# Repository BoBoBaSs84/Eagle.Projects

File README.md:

# Eagle.Projects

All of my Autodesk EAGLE projects are stored here.

## List of projects

- [Medium Wave Radio Transmitter](https://github.com/BoBoBaSs84/Eagle.Projects/tree/main/projects/MediumWaveRadioTransmitter)
- [Morley Power Wah Boost](https://github.com/BoBoBaSs84/Eagle.Projects/tree/main/projects/MorleyPowerWahBoost)
- [RGB Test Pattern Generator](https://github.com/BoBoBaSs84/Eagle.Projects/tree/main/projects/RGB-TestPatternGenerator)

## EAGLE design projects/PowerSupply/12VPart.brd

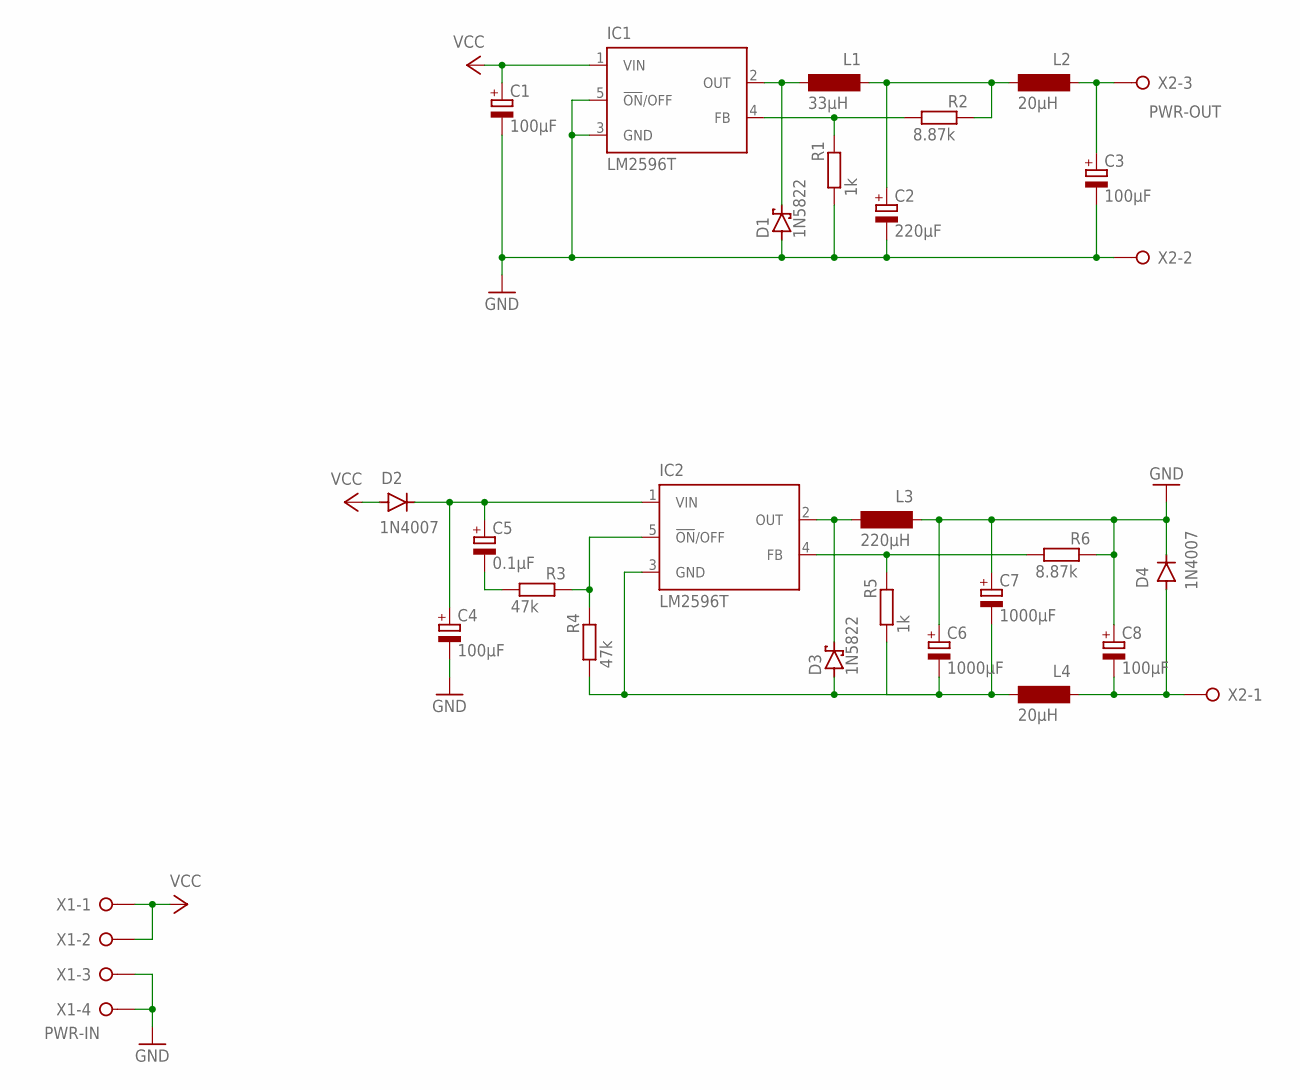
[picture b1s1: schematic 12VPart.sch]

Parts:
C1, C3, C4, C8: 100µF; E2,5-6
C2: 220µF; E2,5-6
C5: 0.1µF; E2-4
C6, C7: 1000µF; E5-10,5
D1, D3: 1N5822; C4111-15
D2, D4: 1N4007; DO-41
IC1, IC2: LM2596T; T05D
L1: 33µH; IND-120
L2, L4: 20µH; B82111B
L3: 220µH; 11PHC
R1, R5: 1k; 0207/10
R2, R6: 8.87k; 0207/10
R3, R4: 47k; 0207/10
X1: PWR-IN; W237-4P
X2: PWR-OUT; W237-133

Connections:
GND: C1.-, C2.-, C3.-, C4.-, C6.+, C7.+, C8.+, D1.A, D4.C, IC1.3 (GND), IC1.5 (!ON!/OFF), L3.P$2 (2), R1.1, R6.2, X1.3, X1.4, X2.2
unnamed: C4.+, C5.+, D2.C, IC2.1 (VIN)
unnamed: C8.-, D4.A, L4.P$2 (2), X2.1
unnamed: D1.C, IC1.2 (OUT), L1.P$1 (1)
unnamed: IC1.4 (FB), R1.2, R2.1
unnamed: C2.+, L1.P$2 (2), L2.P$1 (1), R2.2
unnamed: C3.+, L2.P$2 (2), X2.3
unnamed: C5.-, R3.1
unnamed: IC2.5 (!ON!/OFF), R3.2, R4.2
unnamed: C6.-, C7.-, D3.A, IC2.3 (GND), L4.P$1 (1), R4.1, R5.1
unnamed: D3.C, IC2.2 (OUT), L3.P$1 (1)
unnamed: IC2.4 (FB), R5.2, R6.1
VCC: C1.+, D2.A, IC1.1 (VIN), X1.1, X1.2

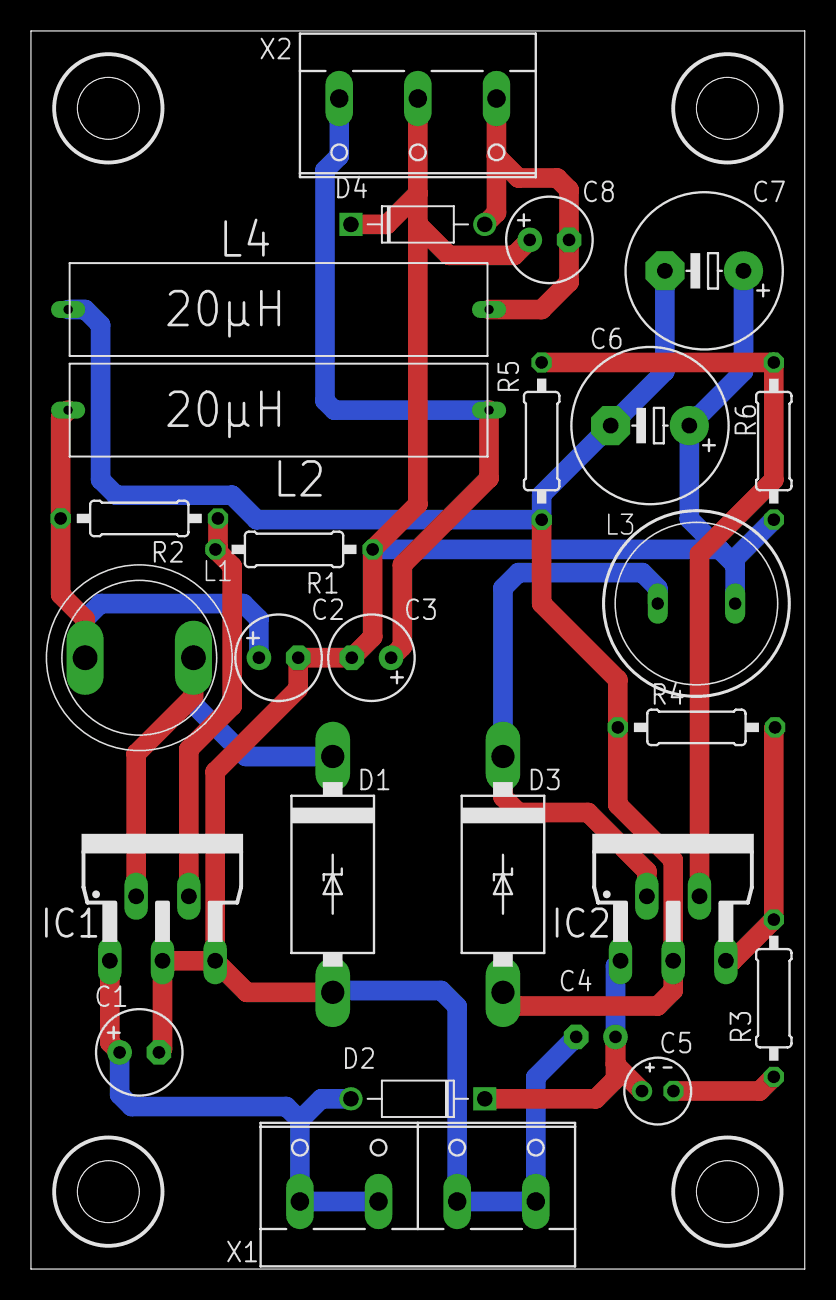
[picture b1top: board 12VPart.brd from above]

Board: 2 copper layers, 50.0 x 80.0 mm, 26 parts (1 on the bottom side), 13 nets.

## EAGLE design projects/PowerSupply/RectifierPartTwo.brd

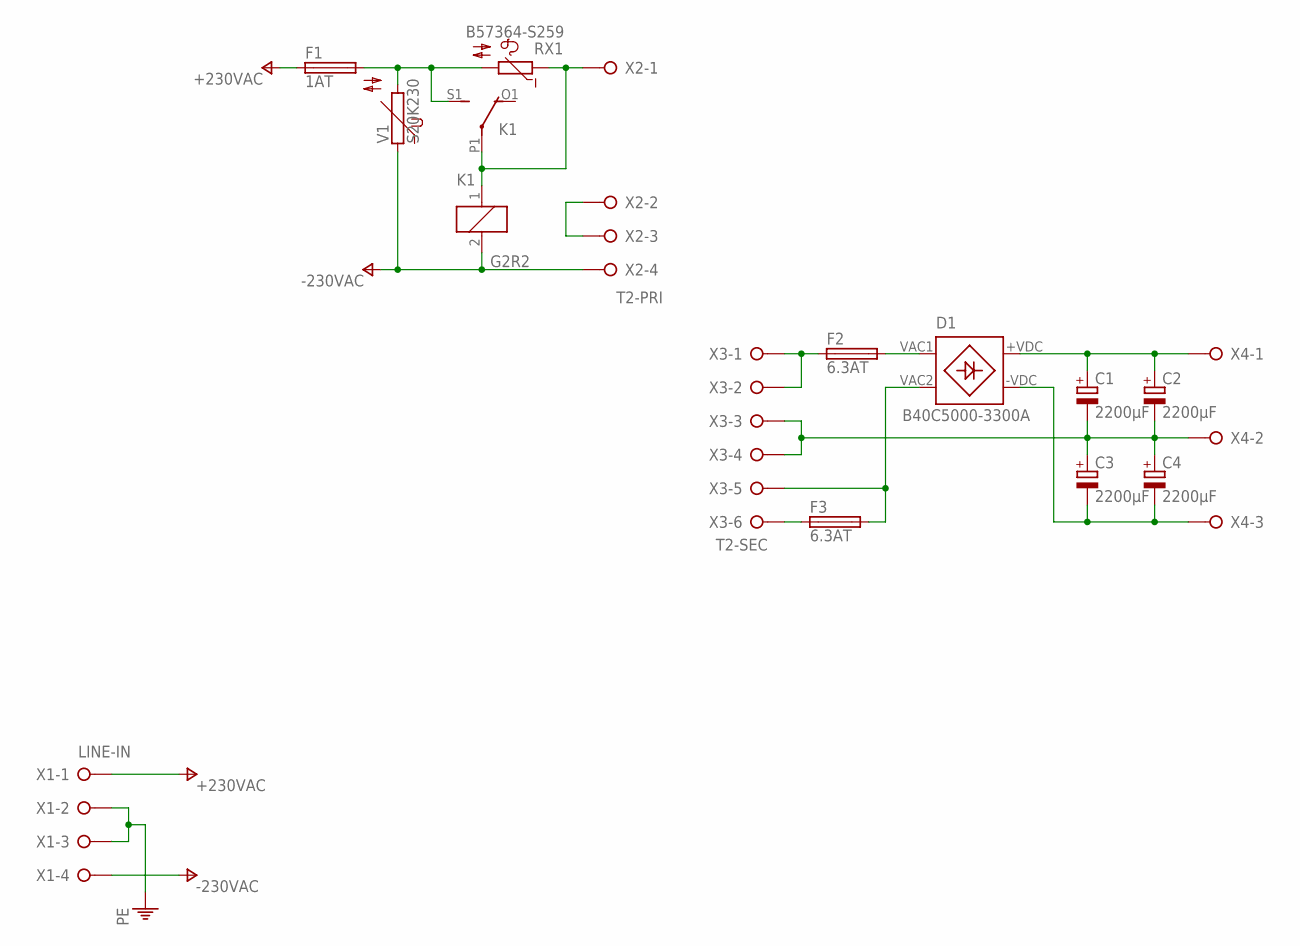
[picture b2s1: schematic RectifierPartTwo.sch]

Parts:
C1, C2, C3, C4: 2200µF; E7,5-16
D1: B40C5000-3300A; B..C
F1: 1AT; SH22,5A
F2, F3: 6.3AT; SH22,5A
K1: G2R2
RX1: B57364-S259; B57364S0
V1: S20K230
X1: LINE-IN; W237-4P
X2: T2-PRI; W237-4P
X3: T2-SEC; W237-6P
X4: W237-03P; W237-133

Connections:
+230VAC: F1.1, X1.1
-230VAC: K1.2, V1.1, X1.4, X2.4
unnamed: D1.VAC2, F3.2, X3.5
unnamed: F2.1, X3.1, X3.2
unnamed: C3.-, C4.-, D1.-VDC, X4.3
unnamed: F3.1, X3.6
unnamed: C1.+, C2.+, D1.+VDC, X4.1
unnamed: C1.-, C2.-, C3.+, C4.+, X3.3, X3.4, X4.2
unnamed: D1.VAC1, F2.2
unnamed: F1.2, K1.S1 (S), RX1.P$2 (2), V1.2
unnamed: X2.2, X2.3
unnamed: K1.1, K1.P1, RX1.P$1 (1), X2.1
PE: X1.2, X1.3

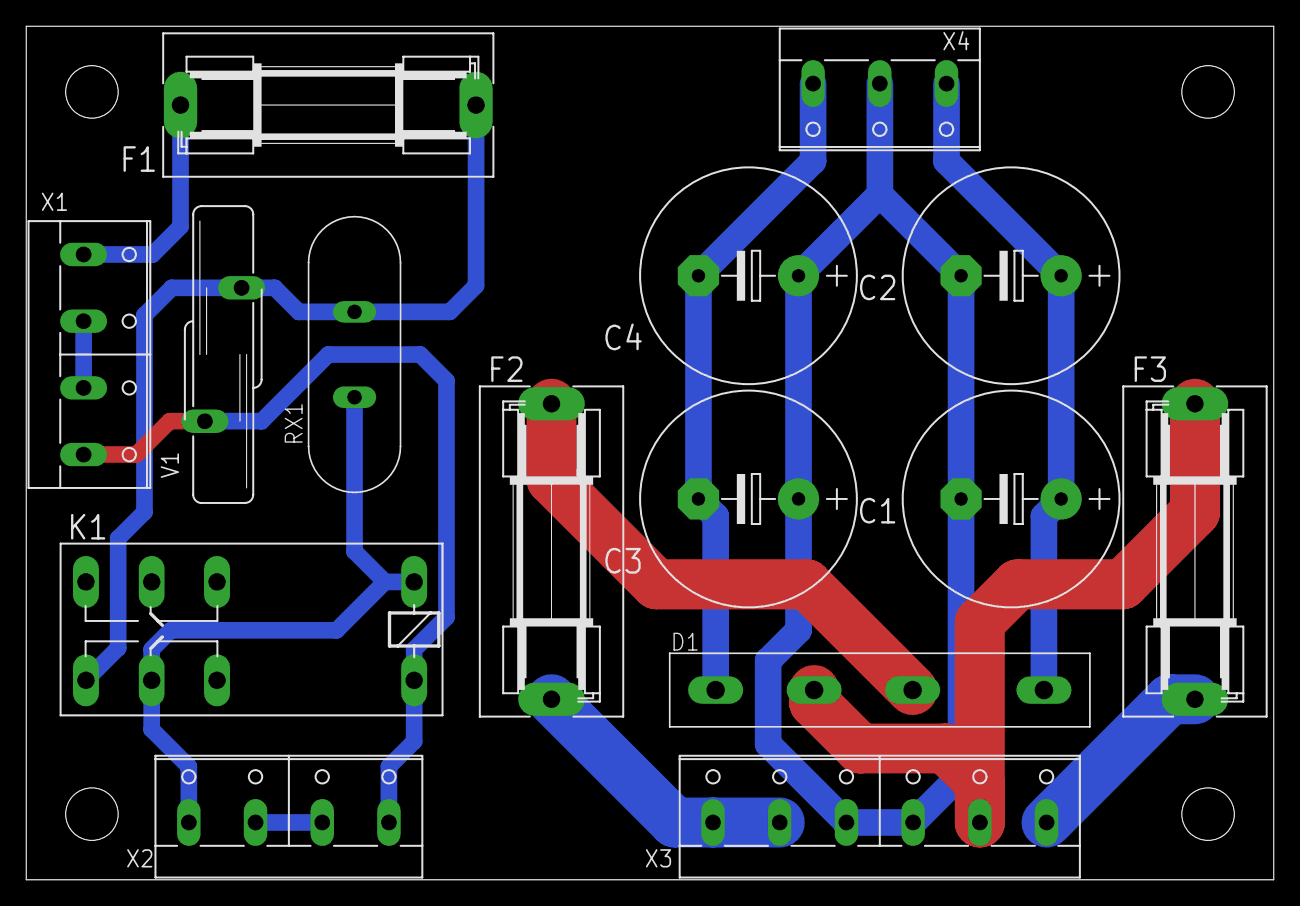
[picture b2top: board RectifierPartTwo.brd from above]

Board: 2 copper layers, 95.0 x 65.0 mm, 15 parts (0 on the bottom side), 13 nets.

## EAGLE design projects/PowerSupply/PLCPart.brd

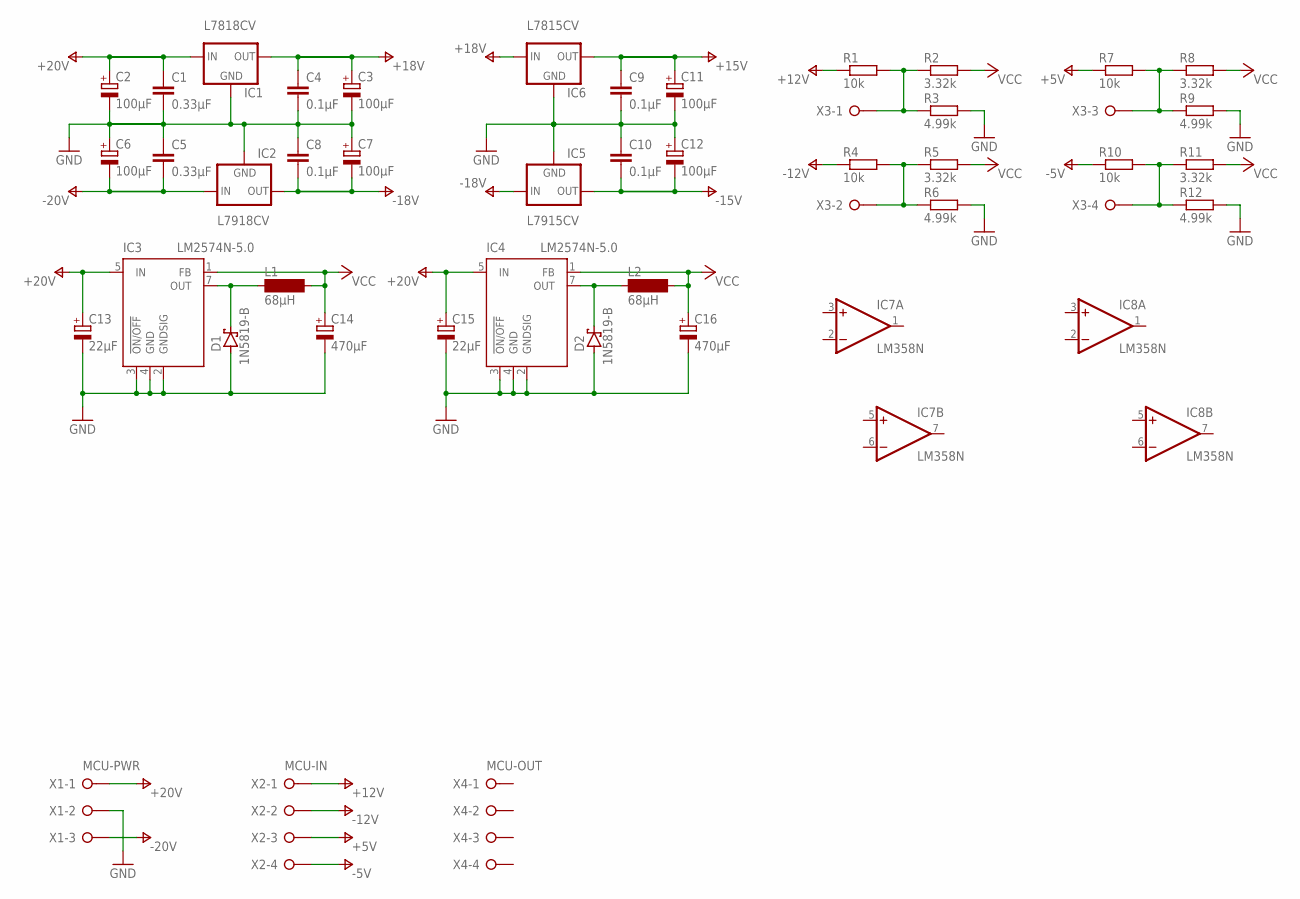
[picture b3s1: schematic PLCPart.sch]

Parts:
C1, C5: 0.33µF; C050-024X044
C2, C3, C6, C7, C11, C12: 100µF; E2,5-6
C4, C8, C9, C10: 0.1µF; C050-024X044
C13, C15: 22µF; E2-5
C14, C16: 470µF; E2-5
D1, D2: 1N5819-B; DO41-7.6
IC1: L7818CV; 78XXS
IC2: L7918CV; 79XXS
IC3, IC4: LM2574N-5.0; DIL08
IC5: L7915CV; 79XXS
IC6: L7815CV; 78XXS
IC7, IC8: LM358N; DIL08
L1, L2: 68µH; SD12K100
R1, R4, R7, R10: 10k; 0207/10
R2, R5, R8, R11: 3.32k; 0207/10
R3, R6, R9, R12: 4.99k; 0207/10
X1: MCU-PWR; W237-133
X2: MCU-IN; W237-4P
X3: W237-04P; W237-4P
X4: MCU-OUT; W237-4P

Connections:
+5V: R7.1, X2.3
+12V: R1.1, X2.1
+15V: C9.1, C11.+, IC6.OUT
+18V: C3.+, C4.1, IC1.OUT, IC6.IN
+20V: C1.1, C2.+, C13.+, C15.+, IC1.IN, IC3.5 (IN), IC4.5 (IN), X1.1
-5V: R10.1, X2.4
-12V: R4.1, X2.2
-15V: C10.2, C12.-, IC5.OUT
-18V: C7.-, C8.2, IC2.OUT, IC5.IN
-20V: C5.2, C6.-, IC2.IN, X1.3
GND: C1.2, C2.-, C3.-, C4.2, C5.1, C6.+, C7.+, C8.1, C9.2, C10.1, C11.-, C12.+, C13.-, C14.-, C15.-, C16.-, D1.A, D2.A, IC1.GND, IC2.GND, IC3.2 (GNDSIG), IC3.3 (!ON/OFF), IC3.4 (GND), IC4.2 (GNDSIG), IC4.3 (!ON/OFF), IC4.4 (GND), IC5.GND, IC6.GND, R3.2, R6.2, R9.2, R12.2, X1.2
unnamed: R1.2, R2.1, R3.1, X3.1
unnamed: R4.2, R5.1, R6.1, X3.2
unnamed: R7.2, R8.1, R9.1, X3.3
unnamed: R10.2, R11.1, R12.1, X3.4
unnamed: D1.C, IC3.7 (OUT), L1.1
unnamed: D2.C, IC4.7 (OUT), L2.1
V+: IC7.8 (V+), IC8.8 (V+)
V-: IC7.4 (V-), IC8.4 (V-)
VCC: C14.+, C16.+, IC3.1 (FB), IC4.1 (FB), L1.2, L2.2, R2.2, R5.2, R8.2, R11.2

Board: 2 copper layers, 44 parts (0 on the bottom side), 20 nets, no tracks yet.

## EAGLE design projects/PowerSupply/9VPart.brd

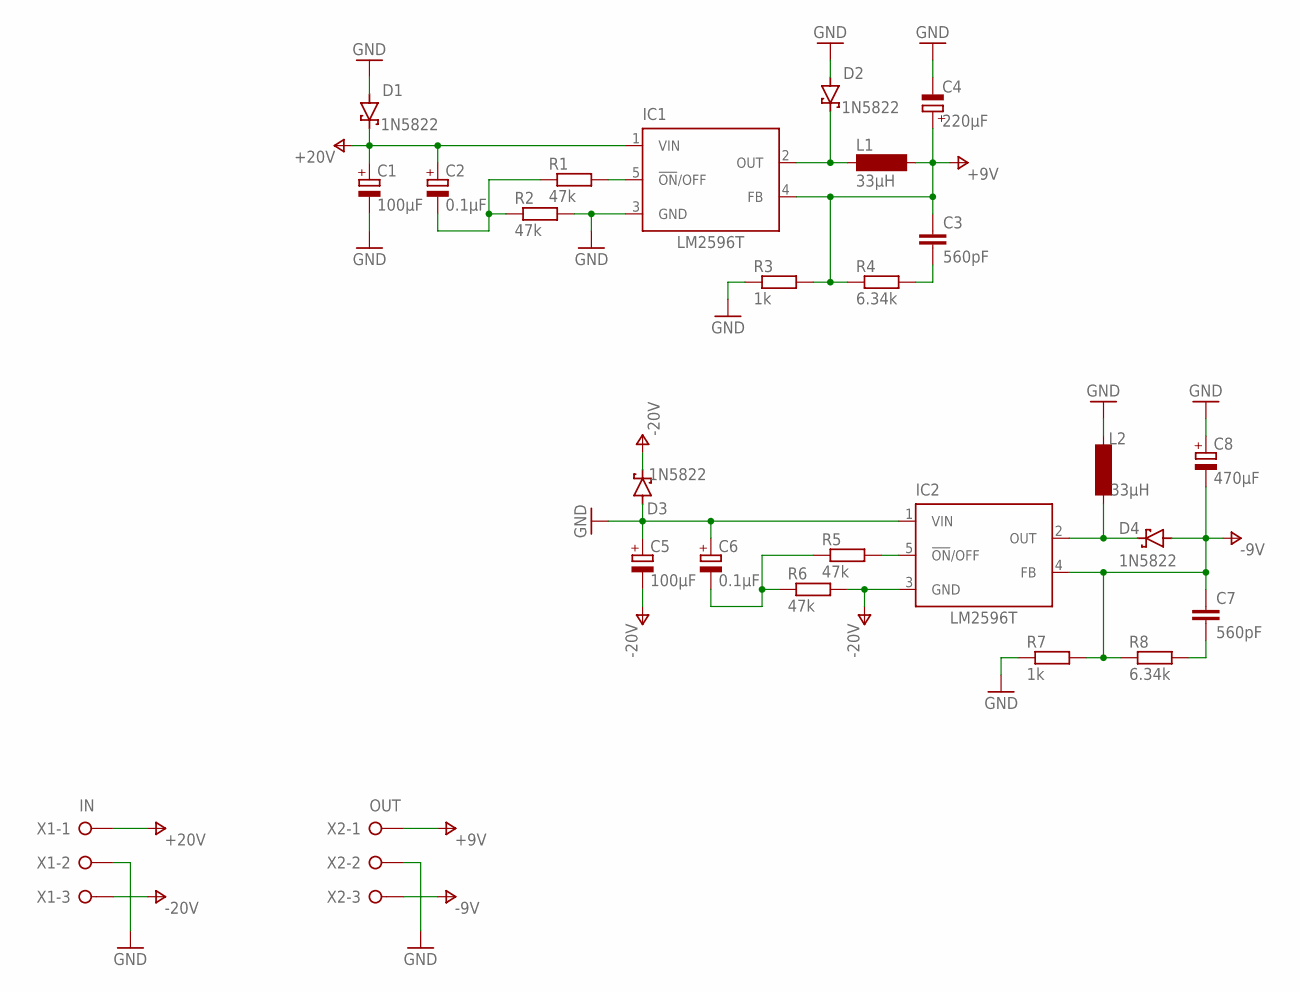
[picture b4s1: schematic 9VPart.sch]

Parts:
C1, C5: 100µF; E2,5-6
C2, C6: 0.1µF; E1,8-4
C3, C7: 560pF; C050-024X044
C4: 220µF; E3,5-8
C8: 470µF; E3,5-8
D1, D2, D3, D4: 1N5822; C4111-15
IC1, IC2: LM2596T; T05D
L1, L2: 33µH; IND-120
R1, R2, R5, R6: 47k; 0207/10
R3, R7: 1k; 0207/10
R4, R8: 6.34k; 0207/10
X1: IN; W237-133
X2: OUT; W237-133

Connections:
+9V: C3.1, C4.+, IC1.4 (FB), L1.P$2 (2), R3.2, R4.1, X2.1
+20V: C1.+, C2.+, D1.C, IC1.1 (VIN), X1.1
-9V: C7.1, C8.-, D4.A, IC2.4 (FB), R7.2, R8.1, X2.3
-20V: C5.-, D3.C, IC2.3 (GND), R6.2, X1.3
GND: C1.-, C4.-, C5.+, C6.+, C8.+, D1.A, D2.A, D3.A, IC1.3 (GND), IC2.1 (VIN), L2.P$2 (2), R2.2, R3.1, R7.1, X1.2, X2.2
unnamed: C3.2, R4.2
unnamed: D4.C, IC2.2 (OUT), L2.P$1 (1)
unnamed: D2.C, IC1.2 (OUT), L1.P$1 (1)
unnamed: IC1.5 (!ON!/OFF), R1.2
unnamed: C7.2, R8.2
unnamed: C2.-, R1.1, R2.1
unnamed: IC2.5 (!ON!/OFF), R5.2
unnamed: C6.-, R5.1, R6.1

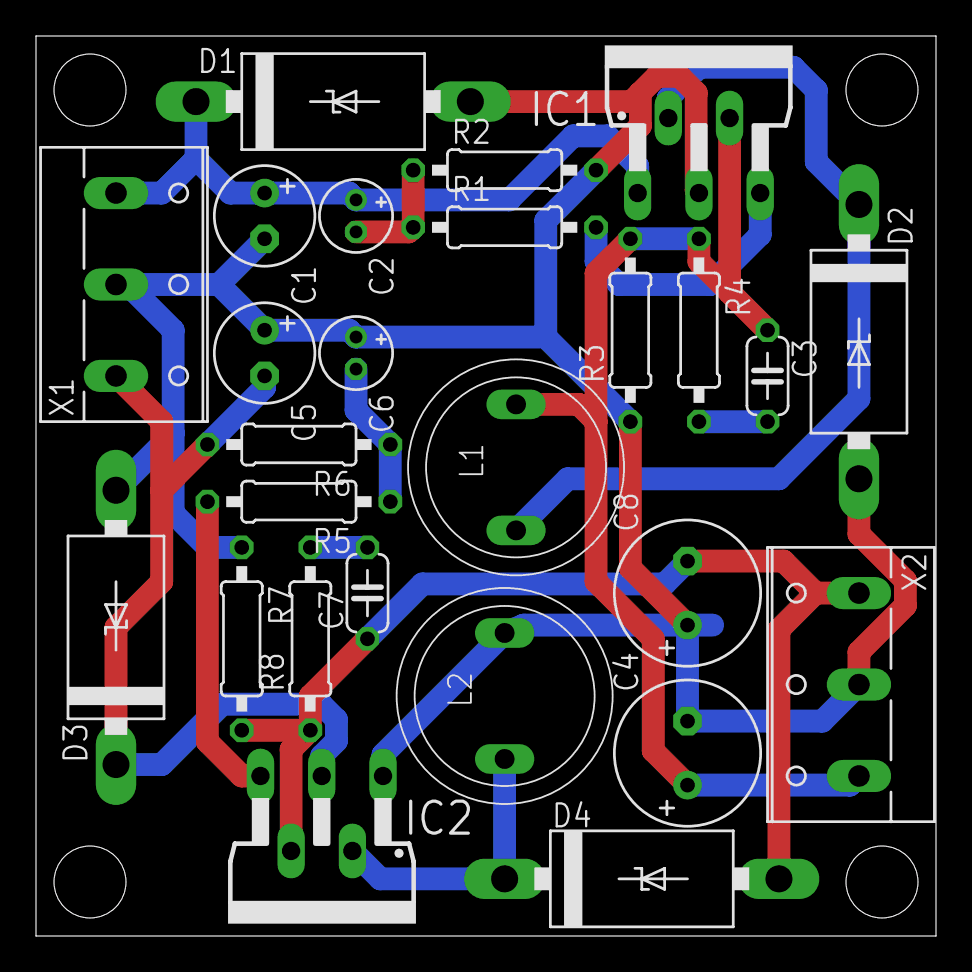
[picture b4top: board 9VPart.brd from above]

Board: 2 copper layers, 50.0 x 50.0 mm, 26 parts (0 on the bottom side), 13 nets.

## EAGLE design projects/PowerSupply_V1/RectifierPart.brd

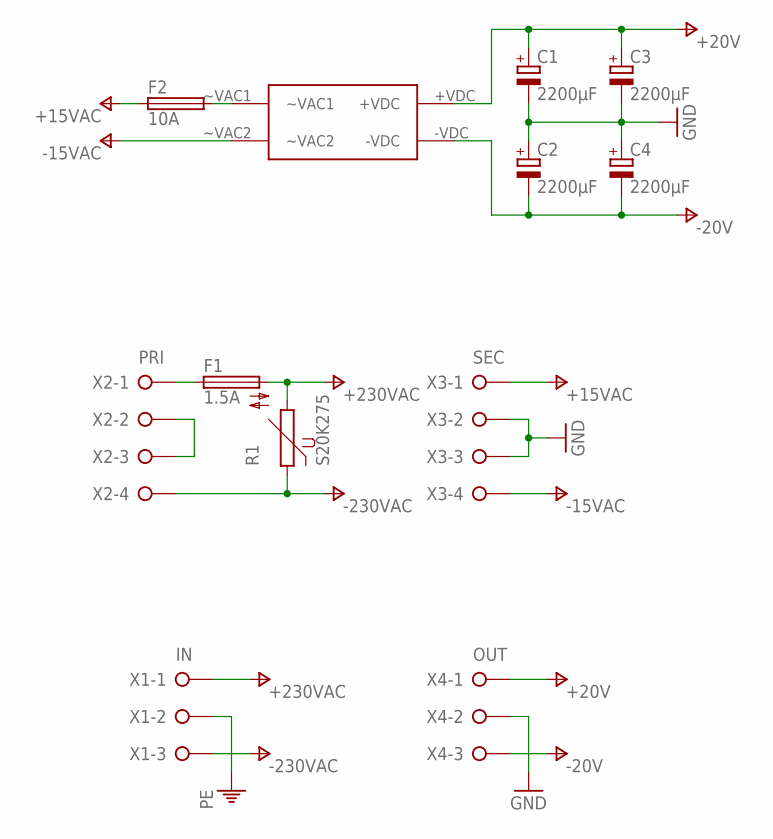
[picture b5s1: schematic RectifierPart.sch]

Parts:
C1, C2, C3, C4: 2200µF; E7,5-16
F1: 1.5A; SH22,5A
F2: 10A; SH22,5A
R1: S20K275
R+1: B40C5000-3300A; B..C
X1: IN; W237-133
X2: PRI; W237-4P
X3: SEC; W237-4P
X4: OUT; W237-133

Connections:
+15VAC: F2.1, X3.1
+20V: C1.+, C3.+, R+1.+VDC, X4.1
+230VAC: F1.2, R1.2, X1.1
-15VAC: R+1.~VAC2, X3.4
-20V: C2.-, C4.-, R+1.-VDC, X4.3
-230VAC: R1.1, X1.3, X2.4
GND: C1.-, C2.+, C3.-, C4.+, X3.2, X3.3, X4.2
unnamed: F2.2, R+1.~VAC1
unnamed: X2.2, X2.3
unnamed: F1.1, X2.1
PE: X1.2

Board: 2 copper layers, 12 parts (0 on the bottom side), 10 nets, no tracks yet.

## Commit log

2024-03-03 chore: initial commit
2024-03-03 feat: rgb drawing
2024-03-05 feat: rgb schematic
2024-03-05 feat: rgb layout
    changes:
    - layout added
2024-03-07 feat: rgb layout
    chnages:
    - schematic modified
    - layout modified
2024-03-07 feat: rgb layout
2024-03-19 well well well
2024-03-19 well, this should do it for now ..
2024-07-19 feat: power supply
2024-07-20 feat: power supply
    changes:
    - first version added
    - second version added
2024-07-20 feat: power supply
    changes:
    - version one done
2024-07-21 feat: power supply
    changes:
    - small fixes to rectifier capacity
2024-09-04 feat: drawing started
2024-09-05 feat: led cube control
    closes #9
2024-09-05 feat: led cube control
    changes:
    - layout added
    closes #10
    Related Work Items: #1
2024-09-05 fix: small fixes applied
2024-09-08 fix: mwrt fixed a little bit
2024-09-08 feat: mpw started
2024-09-09 fix: Medium Wave Radio Transmitter fixes applied
2024-09-09 feat: pwr fixes
2024-09-16 fix: deleted varoius files
2024-09-16 fix: drawing fixed, layout removed
2024-09-16 fix: new layout added
2024-09-16 fix: layout fixed and cam data added
2024-09-22 fix: led cube drawimg fixed
2024-09-22 fix: led control layout fixed
2024-09-22 fix: capacitor value fixed
2024-09-23 feat: led cube control gerber added
2024-09-23 feat: rgb test pattern gerber added
2024-09-23 feat: medium wave transmiter gerber added
2024-10-08 fix: medium wave radio transmitter
    changes:
    - schematic fixed (capacitor packages)
    - routing fixed (capacitor packages)
    - new gerber files added
2024-10-09 fix: mwrt and led control fixed
2024-10-13 feat: 5V part refactored
    changes:
    - schematic changed
    - layout changed
    - gerber files added
2024-10-13 feat: 9V part refactored
    changes:
    - schematic changed
    - layout changed
    - gerber files added
2024-10-13 feat: 12V part refactored
    changes:
    - schematic changed
    - layout changed
    - gerber files addeda
2024-10-13 feat: 15V part refactored
    changes:
    - schematic changed
    - layout changed
    - gerber files addeda
2024-11-10 refactor(5v): schematics changed
2024-11-10 refactor(5v): routing changed
2024-11-10 refactor(5v): new cam files added
2024-11-10 refactor(12v): schematics changed
2024-11-10 refactor(1v): routing changed
2024-11-10 refactor(all): schematics and routing changed
2024-11-10 refactor(15v): schematics and routing changed
2024-11-11 feat(rectifier): schematics changed
2024-11-11 feat(rectifier): schematics and routing changed
2024-11-30 feat: removed old cam files
2024-11-30 feat: rectifier power sources modified
2024-12-21 feat: 5VPart refactored
2024-12-21 feat: 5VParts cam files added
2024-12-21 feat: 12VPart refactored
2024-12-21 feat: 12VPart cam files added
2024-12-21 feat: 9VPart refactored
2024-12-21 feat: 9VPart cam files added
2024-12-21 feat: 15VPart refactored
2024-12-21 feat: 15VPart cam files added
2024-12-21 feat: rectifier part modified
2024-12-21 feat: rectifier part refactored
2024-12-22 feat: old cam files removed
2024-12-22 feat: small fixes and changes applied
2024-12-22 feat: new cam files added
2024-12-22 feat: rectifier part routing finished
2024-12-22 feat: rectifier part cam files added
2024-12-22 fix: drawing fix applied
2024-12-30 chore: gitattributes file added
2024-12-30 feat: power supply project moved
2024-12-30 feat: old project removed
2024-12-30 feat: power supply plc part started
2024-12-30 fix: small fix applied
2024-12-30 feat: amplifiers added
2024-12-30 feat: operation amplifiers finished
2025-01-03 feat: plc part improved
2025-01-03 feat: plc part small fixes applied
2025-01-03 feat: plc part 15 volts added
2025-01-04 feat: plc part op amps (lm358) added
2025-01-04 feat: plc part modified
2025-01-05 feat: plc part buck for vcc added
2025-01-05 feat: plc part modified and layout added
2025-01-07 fix(rect): replaced s20k275 with s20k230
2025-01-07 feat: 5v part modified
2025-01-08 feat: rectifier fuse values modified
2025-01-08 feat: 12 volt part modified
2025-01-08 feat: 5 volt part modified
2025-01-08 feat: 9 volt part modified
2025-01-08 feat: 5 volt part rerouted
2025-01-08 feat: new gerber files added
2025-01-12 feat: plca part modified
2025-01-13 feat: five volt part modified
2025-01-17 feat: drawings added
2025-01-28 feat: rectifier changes applied
2025-01-30 feat: rectifier part one modified
2025-01-30 feat: rectifier part two modified
2025-02-03 feat: rectifier parts modified
2025-02-09 feat: 5 volt part schematic and cam files added
2025-03-03 feat: modified 12 volt parts
